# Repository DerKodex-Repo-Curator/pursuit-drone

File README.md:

# PURSUIT-1

A 92 mm quadcopter whose circuit board is its own airframe, built to follow one enrolled person using face and body re-identification.

 · MIT licence

<p align="center"><sub>Rev C board, top and bottom (KiCad renders)</sub></p>

There is no separate frame. The 4-layer FR4 board is the structure, and the motors clamp into rings at the ends of its arms. The board is generated from a Python netlist rather than drawn by hand. The ESP32-S3 flight firmware is written from the IMU registers up. Person detection and identity run off-board on a laptop (ONNX Runtime), which sends attitude and throttle setpoints to the aircraft over WiFi using a wire protocol generated from a single source file.

## Status

**It has not flown yet.**

| | |
|---|---|
| Rev A board | Fabricated and SMD-assembled by JLCPCB, hand-finished, brought up on the bench in August 2026 |
| Rev C board | Released for fabrication: 4 layers, thermal relief on the hand-soldered pads that caused every rev A fault, `preflight.py` 0 failures and 0 warnings |
| Firmware | Builds for the ESP32-S3; 128 host tests cover the flight-critical logic |
| Vision | Holds a lock on an enrolled person through the aircraft's own camera (88 to 92% of frames on the bench) |
| Flight | Hover throttle not yet measured; PID gains are starting values scaled from similar brushed quadcopters, not tuned on this airframe |

Measured on the rev A board:

- **IMU orientation.** The bench orientation test found the ICM-42688-P mounted 180 degrees in yaw relative to the body frame, which would have flipped the aircraft on take-off. The host tests had passed because they use synthetic data. Corrected in `firmware/include/config.h`.
- **Motors.** All four motors and their AO3400A drivers run on battery, each checked individually.
- **Link.** 3,828 command packets sent and 2,551 telemetry packets received with 0 corrupt, while the control loop ran at about 1.09 kHz. Round trip about 20 ms once WiFi modem sleep is disabled (84 ms with it on).
- **Battery sense.** A 50 kΩ divider source let motor PWM corrupt the ADC, which reported a collapse to 1.47 V while a multimeter read 3.64 V. The firmware now rejects impossible samples and takes a median of five, and rev B onwards uses a 10k/10k divider.
- **Power.** With props on, a charged 1S pouch cell sagged from 4.24 V to 3.20 V at 29% duty per motor, below the 3.40 V landing threshold. A high-discharge flight pack is needed before hovering.

Next: measure hover throttle on a scale (the bench tool has a thrust-sweep mode for this), tune each axis with the aircraft restrained, then hover at 1 m. The full procedure and sign-off table are in [`docs/BRINGUP.md`](docs/BRINGUP.md).

## How it fits together

```
laptop                                              aircraft (ESP32-S3)
------                                              -------------------
camera / MJPEG over WiFi
  -> YOLO11n person detection                       IMU (ICM-42688-P) 1 kHz
  -> ByteTrack multi-object tracking                  -> Madgwick 6-axis filter
  -> SCRFD face detection (head ROI)                  -> angle P
  -> ArcFace 512-d embedding                          -> rate PID
  -> person ReID 768-d                                -> mixer, desaturating
  -> 4-state lock machine                             -> phase-staggered PWM
  -> PD visual servo                                VL53L1X 30 Hz + BMP390 50 Hz
                                                      -> fused height, altitude hold
  -> CRC-16 UDP, 30 Hz, 3x redundant  ------------>  watchdog, arming interlocks
                                     <------------  telemetry, 20 Hz
```

**Identity uses two signals with different jobs.** The face acquires the target and re-confirms it, and is strict. Body re-identification only sustains the lock between readable faces. The appearance model updates only on face-confirmed frames, because without that it drifts onto a stranger within a minute. A readable face that scores below 0.15 counts as evidence against the target, not as missing evidence: without that veto, a swap between two people in similar clothing was sustained by appearance alone.

Because the face model reads to about 2.4 m and the follow distance is 3.0 m, the controller periodically closes to 2.0 m to re-confirm identity by face, and backs off if no face appears within 8 s.

**Tested on two real people.** 400 frames from a live webcam, with a second person moving through the frame, crossing in front, and staying after the target left: locked on 98% of frames (391 of 400; 5 coasting, 4 searching), never lost, and never transferred to the other person. Running this test also showed that the second identity previously in the gallery was the same person as the first, so earlier discrimination results had not tested anything.

**The wire protocol is generated, not duplicated.** `vision/gen_protocol_header.py` writes `firmware/include/pursuit_link.h` from `vision/pursuit/protocol.py`, and CI regenerates and diffs it on every push. A cross-language test parses bytes emitted by the Python side through the real firmware parser. Matching struct sizes would not be enough: field order can differ while sizes agree, endianness can be right in one direction only, and a CRC over a different byte range is self-consistent in each language while rejecting everything across the link.

## Stability through the airframe

The outer loop closes through the aircraft itself: pitching to chase a subject moves the camera, which moves where the subject appears in the frame. That path has a DC gain of

```
VIS_PITCH_KP / VFOV_HALF_DEG  =  34 / 26  =  1.31
```

which is above unity. Correcting a subject 12 degrees high commands 15.7 degrees of pitch and moves them further than the original error. With any link delay, it oscillates.

| transport delay | without attitude compensation | with it |
|---|---|---|
| 0 ms | settled | settled |
| 17 ms (one frame) | 7.6 deg peak to peak, growing | settled |
| 102 ms | 22.3 deg peak to peak | settled |
| 187 ms | 33.3 deg peak to peak | settled |
| **stability boundary** | **about 17 ms** | **over 200 ms** |

The measured round trip is about 20 ms, already past the uncompensated boundary. The attitude compensation in `vision/pursuit/geometry.py` is what makes the design work at all. The mass properties are estimates and the motor time constant is a literature value; see [`sim/flight/README.md`](sim/flight/README.md).

```bash
python sim/flight/lag_sweep.py
```

## A face model trained from scratch

The identity layer uses ArcFace, a 174 MB pretrained model. To put a number on that choice, I trained a face embedding from scratch and benchmarked both on the same protocol.

The data is Labeled Faces in the Wild: 4,324 photographs of 158 people. The split is by identity, not by image: 127 people for training and 31 held out and never seen. Splitting by image, as a flat `train_test_split` does, puts the same faces on both sides:

| | AUC | accuracy |
|---|---|---|
| **held-out identities** | 0.845 | **77.3%** |
| identities seen in training | 0.984 | 93.9% |

That is 16.6 points of inflation from the wrong split.

On identical pairs, ArcFace scores 96.4% and the 1.3 MB model 77.3%: 136 times the weights for 19 points. ArcFace is handicapped here by unaligned 62x47 crops (its published LFW figure is 99.8%).

Accuracy is still rising at the full dataset (53.5% at 570 images, 73.1% at 3,720), so more data is the most valuable next step. Embedding width from 16 to 256 makes no difference beyond run-to-run noise, so the model is not width-limited.

Each point is a training run from scratch, recorded in `ml/runs/`:

```bash
ml/.venv/bin/python ml/train_face_embed.py   # ~60 s on an M-series GPU
ml/.venv/bin/python ml/ablations.py
ml/.venv/bin/python ml/plot_all.py
```

`ml/` has its own Python 3.11 environment because PyTorch has no wheels for the Python version the vision stack uses.

## Check it yourself

None of this needs an aircraft, a board or a camera:

```bash
python -m pytest vision/tests -q                  # perception, control, lock, protocol
cd firmware && pio test -e native && cd ..        # flight-critical firmware logic, run on the host
python -m pytest sim/flight -q && python sim/flight/lag_sweep.py
```

Some vision tests skip until the ~295 MB of model weights are fetched (they are not in the repository, and two exceed GitHub's file limit):

```bash
python vision/fetch_models.py
```

Then the full pipeline runs on a laptop webcam with no aircraft:

```bash
python vision/enroll.py --name you --height 1.75
python vision/run.py --target you
```

## Things that were wrong, and how they were caught

- **Yaw feedback was sign-inverted, a guaranteed runaway on the first hover.** The body frame is FLU, so clockwise yaw reads gyro Z negative, but the headers described the frame as "X forward, Y right, Z up", which is left-handed. Fixed in `firmware/src/frame.h`; the closed-loop test converges with the fix and diverges without it.
- **Accelerometer sign convention.** Level and upright, an accelerometer reads +1 g on +Z (the table pushes up), not -1 g. With the sign inverted, the estimate is exactly wrong rather than obviously broken, and the aircraft would "correct" a 30 degree bank by rolling to 60. Caught by a host test.
- **A timestamp bug every unit test passed.** Commands were stamped when built, not when sent, so the round-trip calculation compared two unrelated clocks, fell outside the plausibility window and was silently discarded. Lead compensation stayed at its 150 ms guess against a true 20 ms. Only `vision/tools/e2e_loop.py`, which runs the whole chain with 10% packet loss and 5% corruption, could see it.
- **Redundancy exposed a sequence bug.** `is_newer(5, 5)` returned true, so an exact duplicate was accepted and re-applied. Harmless while each command was sent once; live as soon as the link sent three copies.
- **The camera was tuned for the wrong failure.** `degradation_sweep.py` showed YOLO tolerates sensor noise (2 people found at 4x gain) but fails under motion blur (2 people at 5 px of blur, none at 15 px). The camera now prefers a dark, noisy, short exposure.
- **`LOOP_HZ 1000` was an intention, not a measurement.** Iterations per second hides stalls, so `firmware/src/loopstats.h` records the loop period distribution instead.
- **Bench findings on real hardware**, listed under Status above: the rotated IMU and the corrupted battery ADC.

## Repository layout

```
hardware/       KiCad 10 project: pursuit.kicad_pcb, .kicad_sch, pursuit.pretty/
scripts/        the board is generated, not drawn
                  design.py       netlist, the single source of truth
                  gen_pcb.py      board generator (pcbnew API)
                  gen_sch.py      schematic generator
                  routes.py       routing tables
                  preflight.py    release gate, must exit 0 before ordering
                  release.py      gerbers, drill, renders, PDF, zip, manifest
gerbers/        fabrication output and the JLCPCB upload files

firmware/       ESP32-S3, PlatformIO, two environments
                  src/            madgwick, pid, mixer, motors, icm42688, alt_hold,
                                  rangefinder, bmp390, altitude_fuse, blackbox,
                                  loopstats, benchtest, flight_state, battery
                  test/           host tests; safety-critical code is written
                                  without Arduino headers so it runs on a laptop
                  include/        config.h pin map, generated pursuit_link.h

vision/         off-board perception and control (ONNX Runtime, CoreML)
                  pursuit/        detector, bytetrack, face, reid, gallery, lock,
                                  control, geometry, arbiter, pilot, protocol, link
                  tests/          test suite
                  tools/          e2e_loop.py, degradation_sweep.py
                  sim_drone.py    simulated aircraft for loopback testing

ml/             face-embedding training on LFW, split by identity
sim/flight/     closed-loop plant model and the stability sweep
tools/          blackbox decoder, link checker
docs/           DESIGN.md        how it works and why
                BUILD.md         ordering, assembly, first power-up, mass budget
                BRINGUP.md       bring-up procedure and sign-off table
                VERIFICATION.md  checks run before each release
                AUDIT_REVD.md    defect audit and upgrade plan
```

## Building one

Ordering files, assembly order, first power-up and the mass budget are in [`docs/BUILD.md`](docs/BUILD.md). Work through [`docs/BRINGUP.md`](docs/BRINGUP.md) in order; do not describe any part as working until its sign-off row is filled in from real hardware.

In the UK, a camera drone needs a CAA operator ID and flyer ID even under 250 g. Fly within line of sight, and run person-following tests with a consenting person, indoors or on private open ground, at walking pace.

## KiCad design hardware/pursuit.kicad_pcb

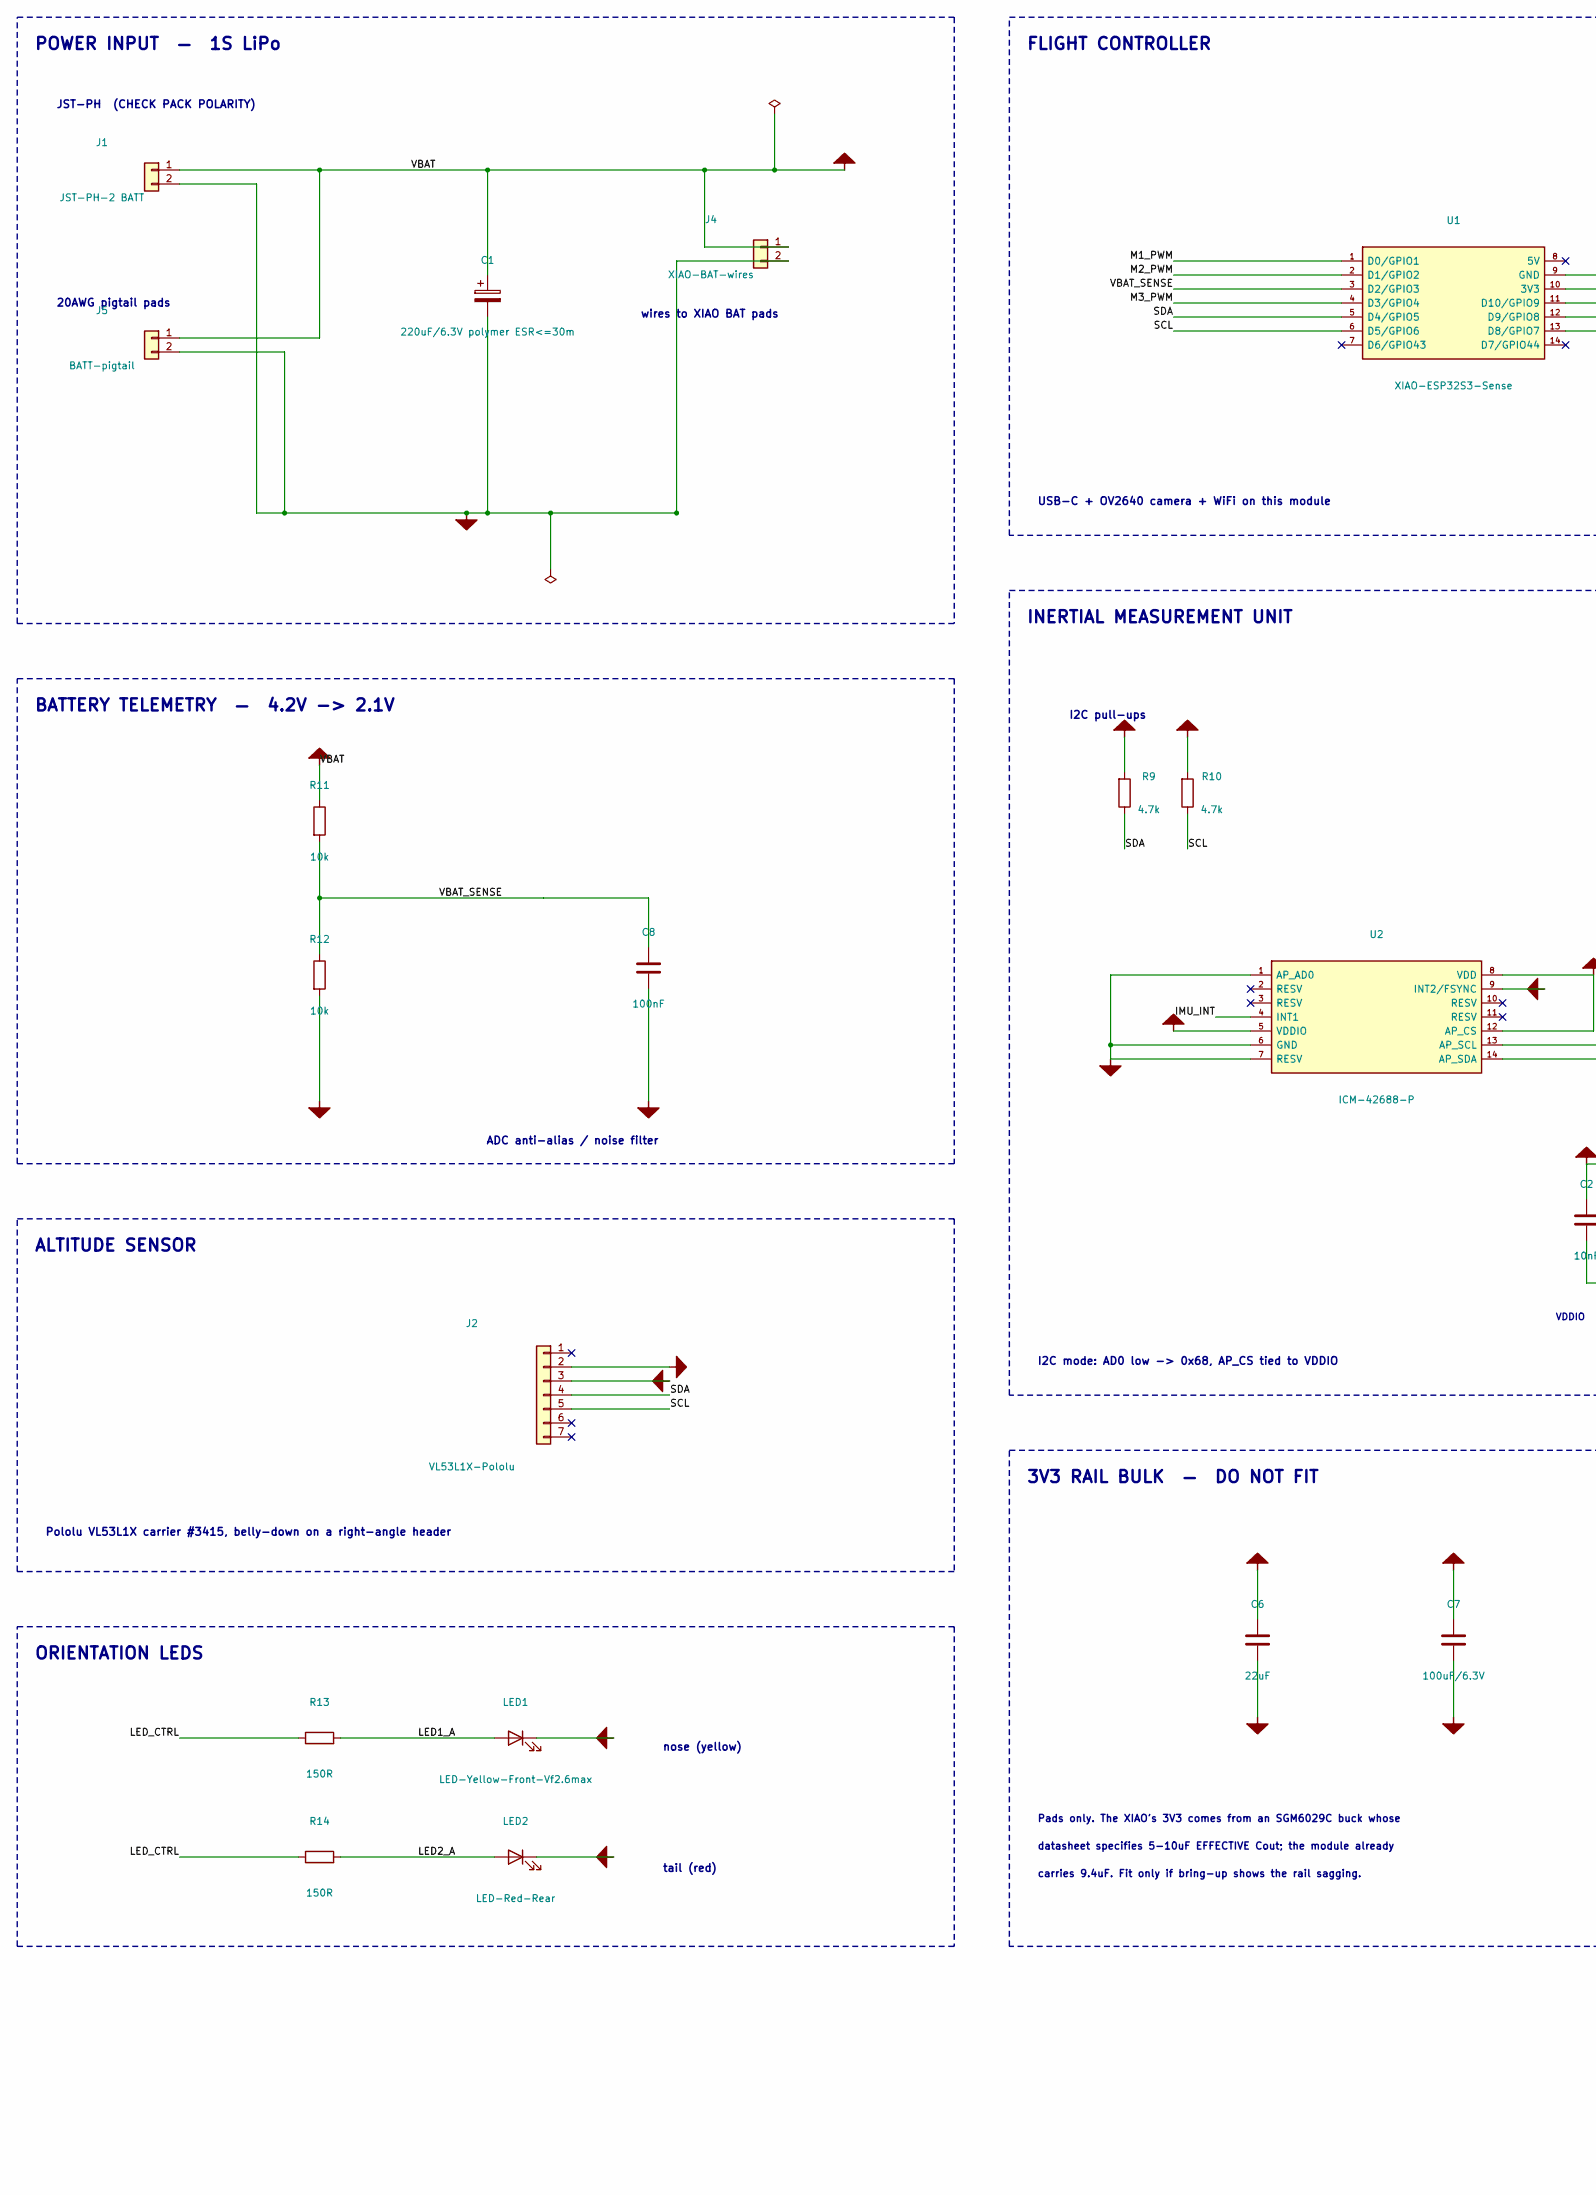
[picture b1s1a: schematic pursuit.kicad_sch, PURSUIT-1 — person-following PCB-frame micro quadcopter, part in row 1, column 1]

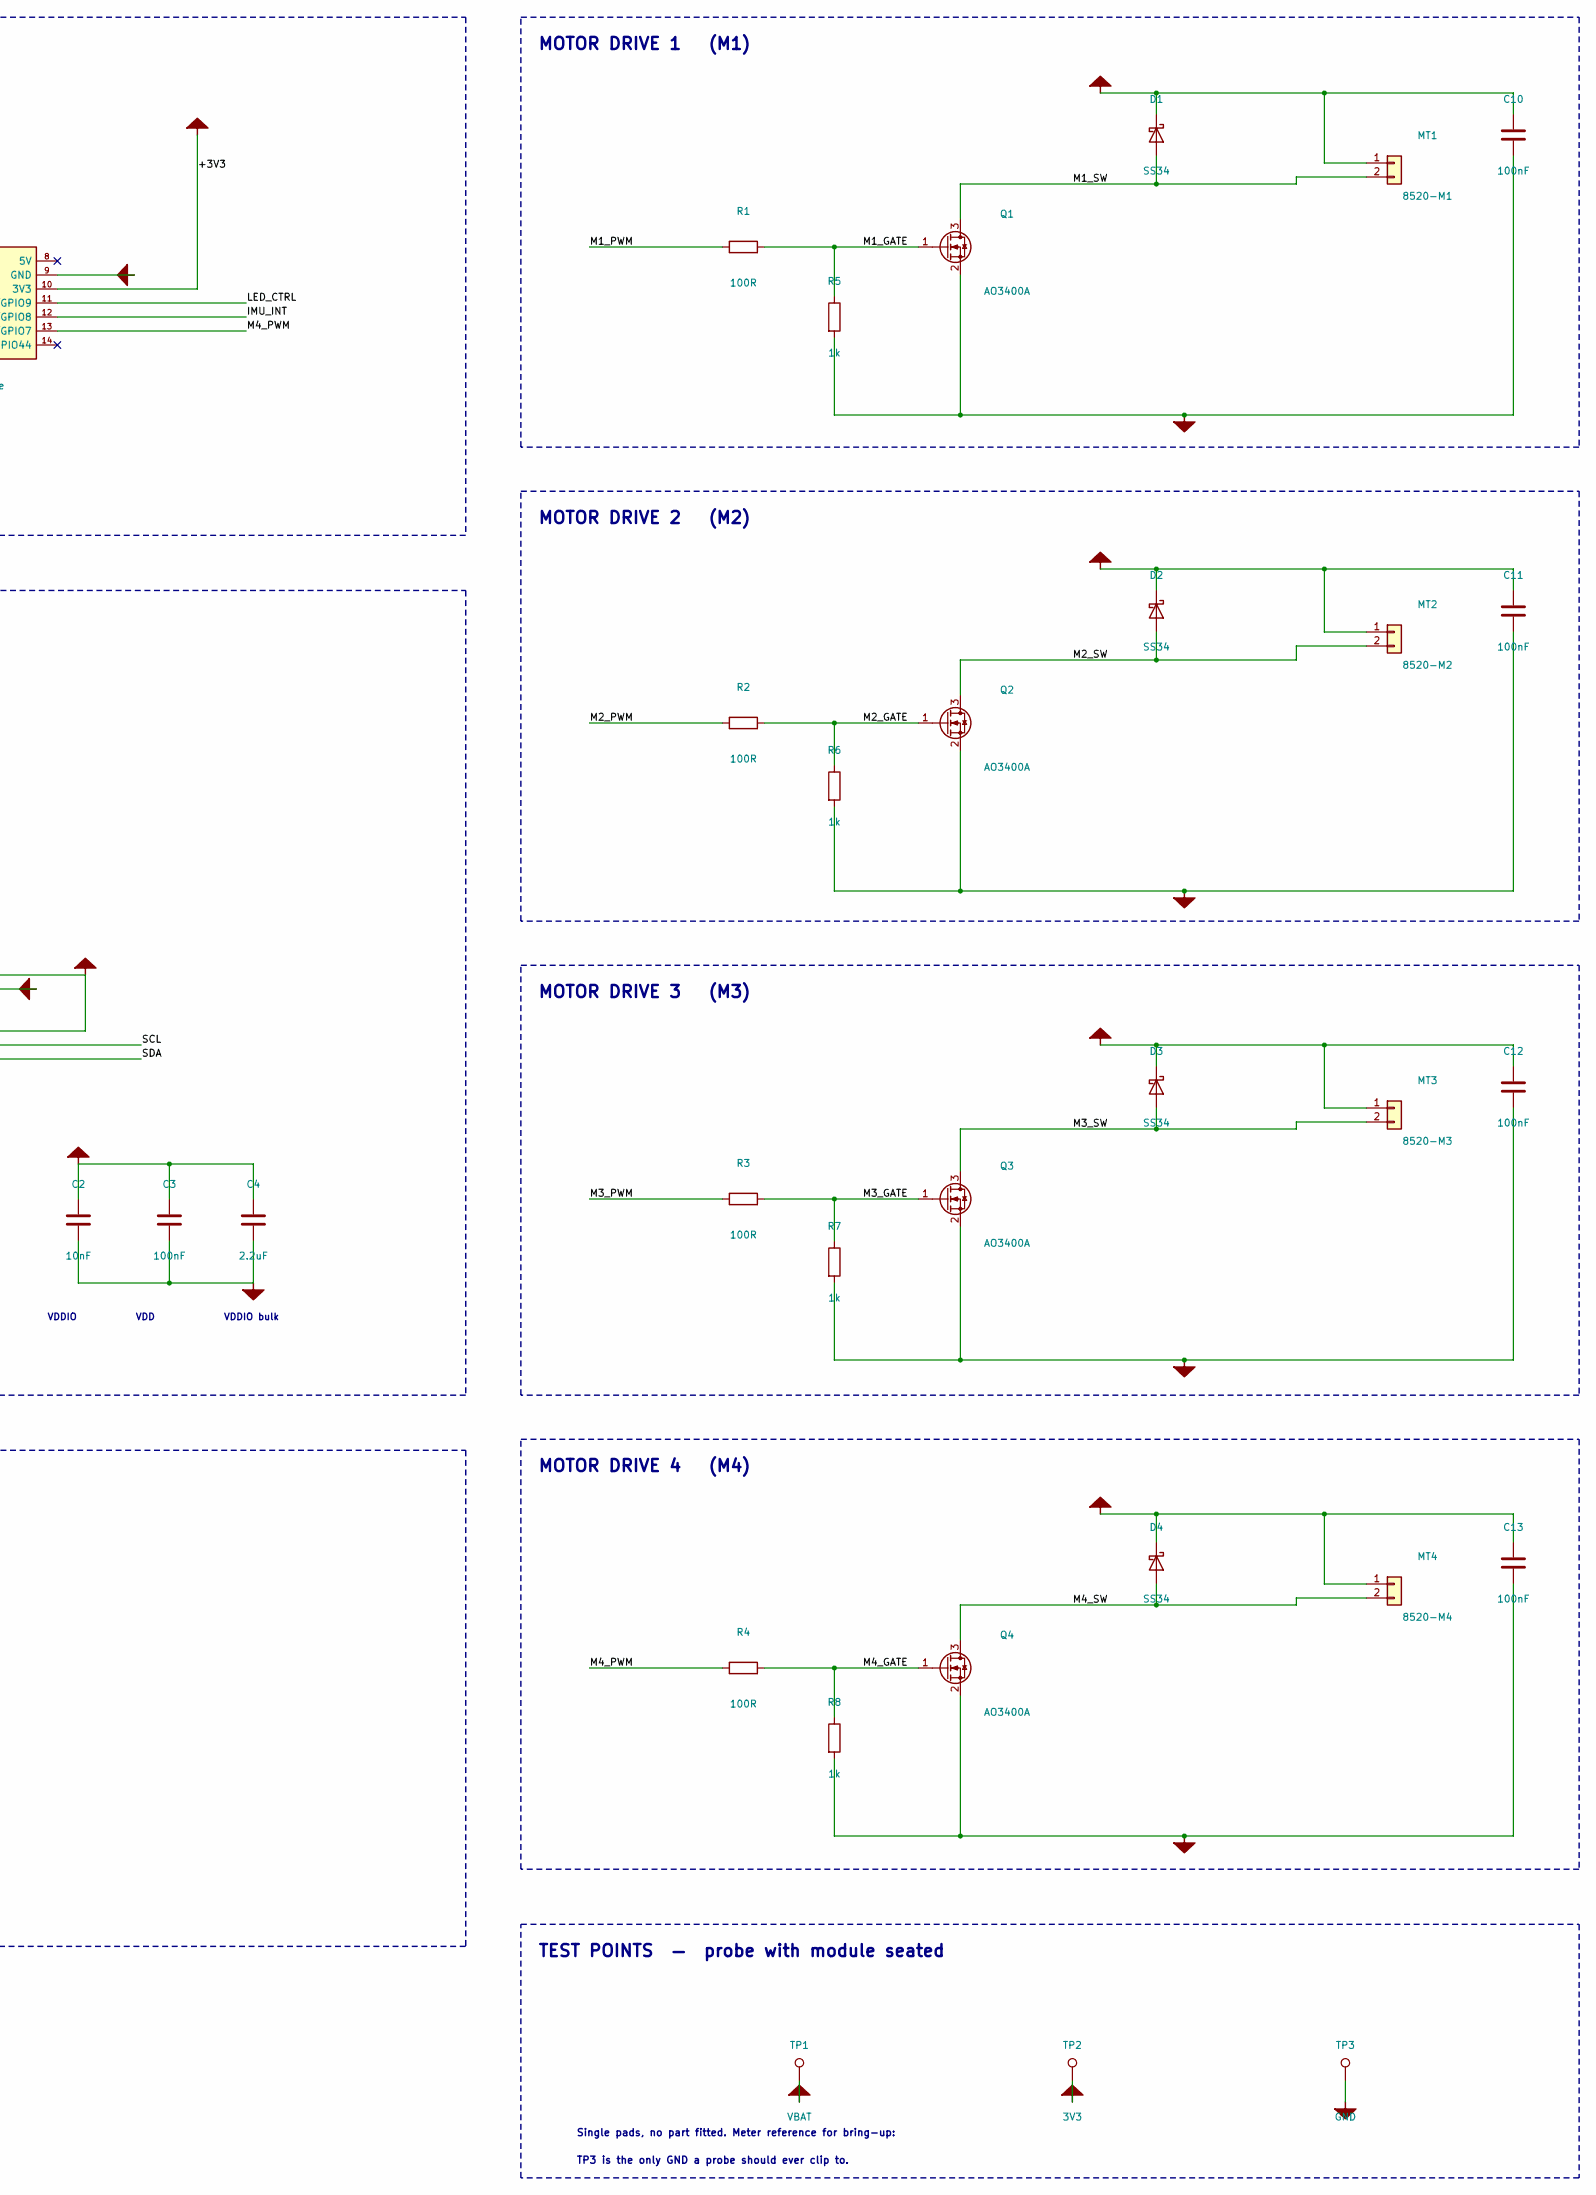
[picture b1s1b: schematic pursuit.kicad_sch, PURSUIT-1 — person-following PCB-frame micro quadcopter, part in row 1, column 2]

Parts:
C1: 220uF/6.3V polymer ESR<=30m; CP_EIA-7343-31_Kemet-D
C2: 10nF; C_0603_1608Metric
C3, C8, C10, C11, C12, C13: 100nF; C_0603_1608Metric
C4: 2.2uF; C_0603_1608Metric
C6: 22uF; C_0805_2012Metric
C7: 100uF/6.3V; C_1206_3216Metric
D1, D2, D3, D4: SS34; D_SMA
J1: JST-PH-2 BATT; JST_PH_S2B-PH-K_1x02_P2.00mm_Horizontal
J2: VL53L1X-Pololu; PinHeader_1x07_P2.54mm_Vertical
J4: XIAO-BAT-wires; Wire_Pads_2x
J5: BATT-pigtail; Wire_Pads_2x_HD
LED1: LED-Yellow-Front-Vf2.6max; LED_0805_2012Metric
LED2: LED-Red-Rear; LED_0805_2012Metric
MT1: 8520-M1; Motor_Pads_2x
MT2: 8520-M2; Motor_Pads_2x
MT3: 8520-M3; Motor_Pads_2x
MT4: 8520-M4; Motor_Pads_2x
Q1, Q2, Q3, Q4: AO3400A; SOT-23
R1, R2, R3, R4: 100R; R_0603_1608Metric
R5, R6, R7, R8: 1k; R_0603_1608Metric
R9, R10: 4.7k; R_0603_1608Metric
R11, R12: 10k; R_0603_1608Metric
R13, R14: 150R; R_0603_1608Metric
TP1: VBAT; TestPoint_1mm
TP2: 3V3; TestPoint_1mm
TP3: GND; TestPoint_1mm
U1: XIAO-ESP32S3-Sense; XIAO_ESP32S3_Carrier
U2: ICM-42688-P; ICM42688P_LGA14

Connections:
+3V3: C2.1, C3.1, C4.1, C6.1, C7.1, J2.2, R9.2, R10.2, TP2.1, U1.10 (3V3), U2.5 (VDDIO), U2.8 (VDD), U2.12 (AP_CS)
IMU_INT: U1.12 (D9/GPIO8), U2.4 (INT1)
LED1_A: LED1.2 (A), R13.2
LED2_A: LED2.2 (A), R14.2
LED_CTRL: R13.1, R14.1, U1.11 (D10/GPIO9)
M1_GATE: Q1.1 (G), R1.2, R5.1
M1_PWM: R1.1, U1.1 (D0/GPIO1)
M1_SW: D1.2 (A), MT1.2, Q1.3 (D)
M2_GATE: Q2.1 (G), R2.2, R6.1
M2_PWM: R2.1, U1.2 (D1/GPIO2)
M2_SW: D2.2 (A), MT2.2, Q2.3 (D)
M3_GATE: Q3.1 (G), R3.2, R7.1
M3_PWM: R3.1, U1.4 (D3/GPIO4)
M3_SW: D3.2 (A), MT3.2, Q3.3 (D)
M4_GATE: Q4.1 (G), R4.2, R8.1
M4_PWM: R4.1, U1.13 (D8/GPIO7)
M4_SW: D4.2 (A), MT4.2, Q4.3 (D)
SCL: J2.5, R10.1, U1.6 (D5/GPIO6), U2.13 (AP_SCL)
SDA: J2.4, R9.1, U1.5 (D4/GPIO5), U2.14 (AP_SDA)
VBAT_SENSE: C8.1, R11.2, R12.1, U1.3 (D2/GPIO3)

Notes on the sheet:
MOTOR DRIVE 1 (M1)
MOTOR DRIVE 2 (M2)
MOTOR DRIVE 3 (M3)
MOTOR DRIVE 4 (M4)
POWER INPUT — 1S LiPo
JST-PH (CHECK PACK POLARITY)
20AWG pigtail pads
wires to XIAO BAT pads
FLIGHT CONTROLLER
USB-C + OV2640 camera + WiFi on this module
INERTIAL MEASUREMENT UNIT
I2C mode: AD0 low -> 0x68, AP_CS tied to VDDIO
I2C pull-ups
VDDIO
VDD
VDDIO bulk
TEST POINTS — probe with module seated
Single pads, no part fitted. Meter reference for bring-up:
TP3 is the only GND a probe should ever clip to.
BATTERY TELEMETRY — 4.2V -> 2.1V
ADC anti-alias / noise filter
ALTITUDE SENSOR
Pololu VL53L1X carrier #3415, belly-down on a right-angle header
ORIENTATION LEDS
nose (yellow)
tail (red)
3V3 RAIL BULK — DO NOT FIT
Pads only. The XIAO's 3V3 comes from an SGM6029C buck whose
datasheet specifies 5-10uF EFFECTIVE Cout; the module already
carries 9.4uF. Fit only if bring-up shows the rail sagging.

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
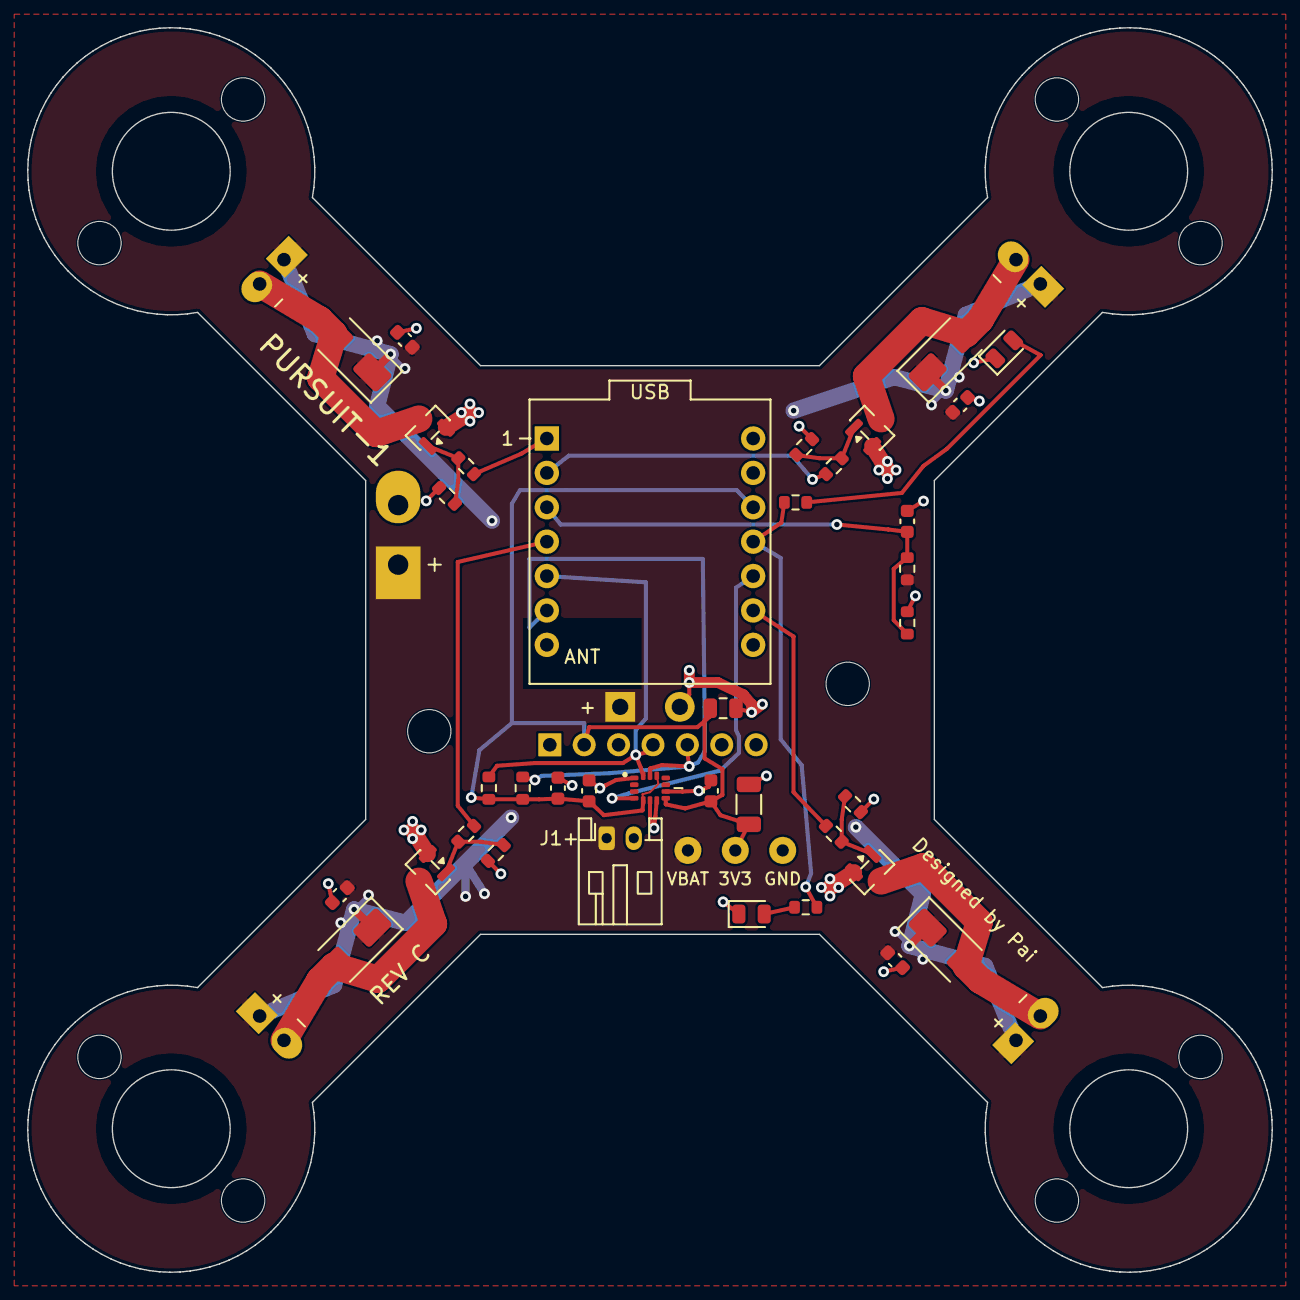
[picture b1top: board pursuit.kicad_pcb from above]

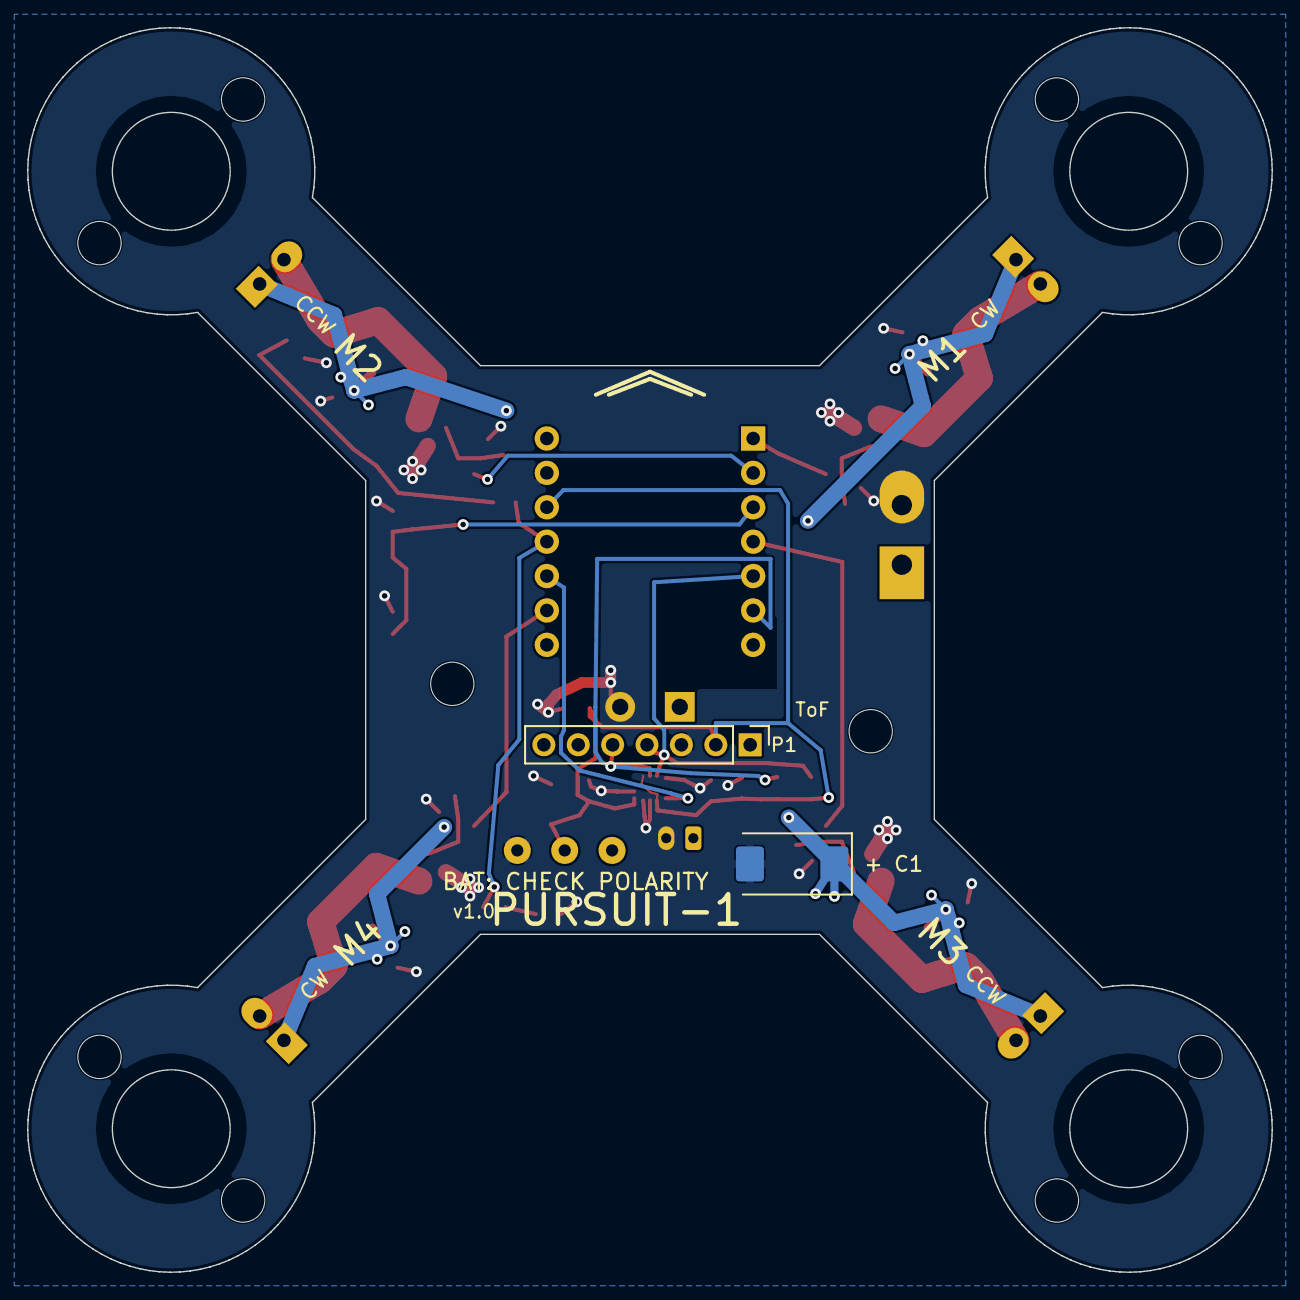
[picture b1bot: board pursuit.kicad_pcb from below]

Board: 4 copper layers, 91.9 x 91.9 mm, 58 parts (2 on the bottom side), 22 nets.

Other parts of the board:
H1, H2, H3, H4, H5, H6, H7, H8, H9, H10: Strap_Hole_3.2

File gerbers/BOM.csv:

Supplied by,Ref,Qty,Value,Package,Part / where to buy,Notes
JLCPCB,U2,1,ICM-42688-P,LGA-14 2.5x3mm,LCSC C1850418 (~USD 17 each; Extended part),"6-axis IMU. LCSC's own MOQ is 100pcs - do NOT try to buy this yourself at qty 1-2, use JLCPCB's PCBA library (or Mouser 410-ICM-42688-P / Farnell for a single). Forces X-ray inspection. MSL1 - no bake. NEVER ultrasonic-clean."
JLCPCB,Q1-Q4,4,AO3400A,SOT-23,LCSC C20917 (~GBP 0.05 ea) - marking A09T,30V 5.7A logic-level NMOS - the standard whoop motor FET
JLCPCB,D1-D4,4,SS34,SMA/DO-214AC,LCSC C8678,3A Schottky flyback. Cathode band faces VBAT (marked on silk)
JLCPCB,R1-R4,4,100R,0603,LCSC C22775,gate series resistors
JLCPCB,R5-R8,4,1k,0603,LCSC C21190,"gate pulldowns - motors stay off during boot. 1k not 10k: it bounds the gate below the AO3400A threshold even against an unexpected ~45k pull-up on a PWM pin (10k would give 0.60V, within 50mV of the 0.65V minimum), and discharges the gate ~10x faster when the pin goes high-Z."
JLCPCB,R9-R10,2,4.7k,0603,LCSC C23162,I2C pullups
JLCPCB,R11-R12,2,10k,0603,LCSC C25804,"battery divider (4.2V -> 2.1V ADC). STOCK LIVE-VERIFIED 2026-08-30 (LCSC: 1,136,900 in stock) - the snapshot zero was stale. If the cart ever disagrees, C2906982 (FRC0603F1002TS) is a verified identical-spec drop-in (Extended, +$3 setup). Do NOT use C23192, it is 510k not 10k. REV B: 10k, was 100k (C25803 - one digit apart, check the line you order). A 100k/100k divider presents ~50k to the ESP32-S3 ADC, which needs <10k to charge its sample-and-hold; during bring-up that produced a textbook-looking battery sag under throttle - r2 ~ 1.0 against PWM duty - that was entirely an artefact of the divider. 10k/10k presents 5k and draws 210uA from the pack."
JLCPCB,R13-R14,2,150R,0603,LCSC C22808,"LED series resistors. 150R not 470R - see the LED rows: with a ~2.0V Vf part on a 3.3V GPIO, 150R gives ~7-8mA."
JLCPCB,C2,1,10nF X7R,0603,LCSC C57112,"IMU bypass at the C2 SITE (routes to U2 pin 5 VDDIO). NOTE: the value<->site mapping is set by the routing - fit exactly what this row says, do not go by the old assumption that C2=100nF."
JLCPCB,C3,1,100nF X7R,0603,LCSC C14663,"IMU bypass at the C3 SITE (routes to U2 pin 8 VDD, 3.9mm away). This is the datasheet-mandated 100nF on VDD."
JLCPCB,C4,1,2.2uF X5R 16V,0603,LCSC C23630 (Extended),IMU bulk on the VDDIO side (TDK BOM)
DO NOT FIT,C6,0,22uF X5R 25V,0805,LCSC C45783 (pads only),"PADS ONLY - deliberately excluded from the JLCPCB BOM/CPL. The XIAO 3V3 rail is an SGM6029C buck whose datasheet recommends 5-10uF EFFECTIVE output capacitance; the module already carries 9.4uF nominal. Fitting C6+C7 put ~50-64uF effective on that node. Only fit if bring-up shows the 3V3 rail actually sagging."
DO NOT FIT,C7,0,100uF X5R 6.3V,1206,LCSC C15008 (pads only),"PADS ONLY - see C6. Adding capacitance to a bare pad takes five minutes; removing a reflowed 1206 sitting 7.3mm from a 0.5mm-pitch LGA does not."
JLCPCB,C8,1,100nF,0603,LCSC C14663,ADC sense filter
JLCPCB,LED1,1,yellow LED 0805,0805,LCSC C84261 (NationStar NCD0805Y1),"FRONT orientation LED. Vf 1.6-2.6V. NOT white or blue: every white/blue 0805 is InGaN with Vf specified as a 2.6-3.6V BIN RANGE, and the upper bins simply never conduct from a 3.3V GPIO. No resistor value fixes that."
JLCPCB,LED2,1,red LED 0805,0805,LCSC C84256 (NationStar NCD0805R1),"REAR orientation LED. Vf 1.6-2.6V. Both LEDs share one GPIO (LED_CTRL) so they are always on together - colour, not blink pattern, is what tells you nose from tail."
YOU,C1,1,220-470uF 6.3V POLYMER ESR<=30mOhm ripple>=2A,7343/D case (2917),"Panasonic 6TPE220MI / 6TPE330MI or Kemet polymer equivalent","BELLY. MUST be polymer/tantalum. POLARITY: the belly silk marks '+ C1' beside pad 1. Reversed across an unfused LiPo this vents."
JLCPCB,C10-C13,4,100nF 16V X7R,0603,LCSC C14663,"VBAT ceramic bypass, one at each flyback. REV C: moved from the BELLY to the TOP face, so JLCPCB places them now - four fewer hand joints, and it keeps the assembly run single-sided. Do not omit: without these nothing on the board handles the MHz content of the switching edges."
YOU,U1,1,Seeed XIAO ESP32S3 Sense **PRE-SOLDERED**,module on 2x 1x7 FEMALE sockets,Seeed 102010635 "XIAO ESP32S3 Sense (Pre-Soldered)" ~USD 14.90 - NOT the bare one,"BUY THE PRE-SOLDERED VERSION and fit FEMALE 2.54mm SOCKET strips to the board, not male pins. Seeed have already soldered the module side, so 14 of the board's 58 hand joints simply do not exist - for about GBP 2. Same THT footprint, so no board change. Two further wins: the module becomes REMOVABLE (a dead XIAO stops meaning a dead board, which has already happened once), and it sits ~8.5mm up instead of ~2.5mm. USB edge faces the board front - marked on silk three ways. Comes with camera + U.FL antenna. NOTE: the Sense expansion board's three 4.7k SD pull-ups (behind solder pad J3) land on D9/MISO, D10/MOSI and SD_CS - i.e. on IMU_INT and LED_CTRL here, both harmless. Cutting J3 is optional and costs the microSD slot, which this build does not use."
YOU,J1,1,JST S2B-PH-K-S,right-angle THT,LCSC C173752 / any,"battery connector. CHECK PACK POLARITY WITH A METER FIRST - JST-PH is not standardized! The top silk marks '+' beside pad 1."
YOU,J2,1,Pololu VL53L1X carrier #3415,7-pin breakout,Pololu 3415 (~GBP 12) via Pimoroni/Mouser,ToF altitude sensor. Mount belly-down on a RIGHT-ANGLE 1x7 header so it lies flat
YOU,J4/J5,-,wire pads,-,-,J4: two short 24AWG wires to the XIAO underside BAT pads. J5: MANDATORY 20AWG battery pigtail — the JST-PH at J1 is rated 2A/contact and SPICE shows 9.82A at full throttle; J1 alone is bench-throttle only, NEVER flight. Preheat the pad (inner VBAT plane heatsinks it), 60W+ iron, tug-test
YOU,MT1-MT4 motors,4,8520 coreless 8.5x20mm,-,"AliExpress/Amazon '8520 motor CW CCW pair' (~GBP 10/4pcs)",Buy 2x CW + 2x CCW. 1.0mm shaft. Verify polarity: red/blue = CW; white/black = CCW (varies by seller!)
YOU,Props,4+spares,65mm 2-blade 1.0mm bore,-,"'65mm prop 8520/720' combo sets, or Hubsan X4 55mm as fallback",MUST be 1.0mm bore - most modern '65mm whoop' props are 1.5mm bore and will NOT fit
YOU,Battery,2+,1S 650mAh HV LiPo whoop stick (PH2.0),~65x19x8mm ~18g,"GNB/Gaoneng or BetaFPV 650mAh 1S HV","650mAh not 450mAh: +5g buys +44% energy, so ~7.2 min hover instead of ~5.4. Same connector, no board change. Also buy a 1S USB charger - the XIAO's ~100mA onboard charge works but is slow."
YOU,Sockets,-,2.54mm FEMALE socket strips,THT,any,"2x 1x7 FEMALE (for the pre-soldered XIAO - see U1) + 1x7 right-angle MALE for the ToF breakout. Female sockets are the whole point: the module plugs in "instead of being soldered down."
YOU,Camera mount,1,foam wedge or printed edge clip,-,-,"No screw holes: every bracket position sat on a drive stage, and metal M2 hardware there would bridge VBAT (head) to GND (nut) through the board. Clip/tape the camera to the front edge."
YOU,Zip ties,8+,2.5mm mini cable ties,-,any,motor retention through the ring holes + battery strap
YOU,Pigtail-J5,1,"20AWG silicone, 60mm, red/black heat-shrink, JST-PH2.0 pack end",-,any,"BUILD AND METER THIS BEFORE ANY PACK IS ON THE BENCH. The only lead that ever plugs into J1. Reversal defence is polarity discipline, not a fuse: a reversed pack drives ~20A through Q1-Q4 body diodes and kills the XIAO in ms, long before any fuse opens. Optional fuse must be <=10mOhm measured (sag margin is 0.11V) and worst_case.cir re-run with it."

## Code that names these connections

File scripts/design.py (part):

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        value="XIAO-ESP32S3-Sense",
        lib=None, footprint="XIAO_ESP32S3_Carrier",
        pins={
            # research-locked: camera/mic use NO header pins; D2=GPIO3 is a
            # strapping pin so it carries only the high-impedance divider;
            # D6/D7 stay as UART (ROM boot log toggles D6 at reset)
            "1": "M1_PWM",       # D0 / GPIO1
            "2": "M2_PWM",       # D1 / GPIO2
            "3": "VBAT_SENSE",   # D2 / GPIO3  ADC1_CH2 (strap pin: high-Z ok)
            "4": "M3_PWM",       # D3 / GPIO4
            "5": "SDA",          # D4 / GPIO5  (XIAO default SDA)
            "6": "SCL",          # D5 / GPIO6  (XIAO default SCL)
            "7": None,           # D6 / GPIO43 U0TXD — debug via USB-C or
                                 # tack wires to the module castellations
            "8": None,           # 5V = USB VBUS passthrough — unconnected
            "9": "GND",          # GND
            "10": "+3V3",        # 3V3 (600 mA buck budget; ~420 mA streaming)
            "11": "LED_CTRL",    # D10 / GPIO9
            "12": "IMU_INT",     # D9  / GPIO8
            "13": "M4_PWM",      # D8  / GPIO7
            "14": None,          # D7  / GPIO44 U0RXD — spare
        },
    ),
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    # at 900dpi to resolve the junction dots, the three 4.7k pull-ups off JP3
    # land as: R4 -> D9/MISO, R5 -> D10/MOSI, R6 -> SD_CS (thence IO21 via
    # R12=0R; R11 to D2 is DNP). **D8/SCK carries only R2 = 22R in series to
    # the socket CLK pin and one ESD clamp — no pull-up.** So M4_PWM is
    # genuinely floating at reset, exactly like M1-M3, and all four gates sit
    # at ~0V with any sane pulldown.
    #
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    # out of a 650mAh pack -- 0.03%, and the aircraft flies for four minutes.
    # Trading 190uA for a battery reading you can believe is not a close call.
    "R11": dict(value="10k", lib="Resistor_SMD", footprint="R_0603_1608Metric",
                pins={"1": "VBAT", "2": "VBAT_SENSE"}),
    "R12": dict(value="10k", lib="Resistor_SMD", footprint="R_0603_1608Metric",
                pins={"1": "VBAT_SENSE", "2": "GND"}),
    "C8": dict(value="100nF", lib="Capacitor_SMD", footprint="C_0603_1608Metric",
               pins={"1": "VBAT_SENSE", "2": "GND"}),

    # -- test points (rev B) -----------------------------------------------
    # One pad per power rail, reachable with a meter probe while the module is
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
    # -- ToF altitude sensor header (belly, faces down) --------------------
    # Pololu 3415 pin order (research-confirmed): VDD VIN GND SDA SCL XSHUT
    # GPIO1. VDD is the breakout's 2.8V regulator OUTPUT — leave NC. XSHUT
    # has an onboard 47k pullup — safe to leave NC.
    # REV C ATTEMPTED AND BACKED OUT: a 4-pin JST-SH surface-mount connector
    # in place of this header. It is the single largest joint reduction on the
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
    # -- Orientation LEDs ---------------------------------------------------
    "R13": dict(value="150R", lib="Resistor_SMD", footprint="R_0603_1608Metric",
                pins={"1": "LED_CTRL", "2": "LED1_A"}),
    # White/blue is NOT an option here. Every white 0805 is an InGaN die with
    # Vf specified as a BIN RANGE of 2.6-3.6V; 2.6V is the bottom of that bin,
    # not the maximum. Driven from a 3.3V GPIO the top bins simply never
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    # the same NationStar 0805 family as the red rear LED, so front and rear
    # stay distinguishable and both light on any bin.
    "LED1": dict(value="LED-Yellow-Front-Vf2.6max", lib="LED_SMD", footprint="LED_0805_2012Metric",
                 pins={"1": "GND", "2": "LED1_A"}),  # 1=K, 2=A
    "R14": dict(value="150R", lib="Resistor_SMD", footprint="R_0603_1608Metric",
                pins={"1": "LED_CTRL", "2": "LED2_A"}),
    "LED2": dict(value="LED-Red-Rear", lib="LED_SMD", footprint="LED_0805_2012Metric",
                 pins={"1": "GND", "2": "LED2_A"}),
}


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

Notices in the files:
README.md:
[](https://github.com/Pai-88/pursuit-drone/actions/workflows/ci.yml) · MIT licence
